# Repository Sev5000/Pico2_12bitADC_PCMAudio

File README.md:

# Pico2_12bitADC_PCMAudio
This is a PCB to neatly package a Raspberry Pi Pico 2, AD9226 ADC PCB and a PCM1802 audio board for capture with hsdaoh.
Specifically designed to still be usefull without smds (no head switch input then). Through-hole only works just fine.
For use with https://github.com/steve-m/hsdaoh-rp2350/tree/pcm1802

Features:
- The Pico 2 can be socketed with and without a DVI sock
- Mounting holes for the AD9226 pcb, PCM1802 and a socketed Pi Pico 2 with DVI sock (original and adafruit verfied)
- Audio input with either chinch or 3.5mm jack
- Jumper to choose between head switch input and clipping bit of the AD9226
- Protected head switch input has footprints for jst, as well as edge and horizontal SMA/SMB

Bill of material: 
- 1x This PCB (Send the Gerber .zip to JLC, PCBWay, ..)
- 1x Raspberry Pi Pico 2
- 1x AD9226: https://aliexpress.com/item/1005003038271519.html
- 1x PCM1802: https://aliexpress.com/item/1005006412873984.html
- 2x RCA-105 or RCA-106: https://aliexpress.com/item/1005006152724809.html
- 1x PJ-324M 5P: https://aliexpress.com/item/1005006146950431.html
- 1x 3pin 2.54mm pin header horizontal for the headswitch/overflow selection jumper
- 1x 9pin 2.54mm pin-socket header 
- 1x 2x10pin 2.54mm pin-socket header
- 1x 3pin 2.54mm pin header (remove the center pin for connecting R/L of the PCM1802)
- 1x 3pin 2.54mm pin-socket header (remove the center pin for connecting R/L of the PCM1802)

No SMD variant:
- 1x DVI-Sock: https://github.com/Wren6991/Pico-DVI-Sock for a flush fit with the pcb edge, otherwise the adafruit DVI sock works fine too
- 2x 15pin 2.54mm pin-socket header

SMD Variant:
- 1× Stewart SS-53000-001 connector (See https://github.com/Wren6991/Pico-DVI-Sock BOM for details)
- 8× 0402 270 ohm resistors
- 5x 0805 100nF ceramic capacitors
- 2x 20pin 2.54mm pin-socket header (For socketed Pi Pico 2 only)

For head switch input:
- 1x SOD123 3.3V zener diode
- 1x SOD123 standard diode
- 1x 0805 1k resistor
- 1x edge SMA/SMB or horizontal SMA/SMB and/or 2pin header

Notes:
The PCM1802 board needs MODE0 (MODE1 only with previous HSDAOH releases) bridged *and* connected to 3.3V with a wire (Those boards have a design error):
NOTE: Picture shows the configuration for the older firmware, now only MODE0 needs to be bridged and connected to 3.3V

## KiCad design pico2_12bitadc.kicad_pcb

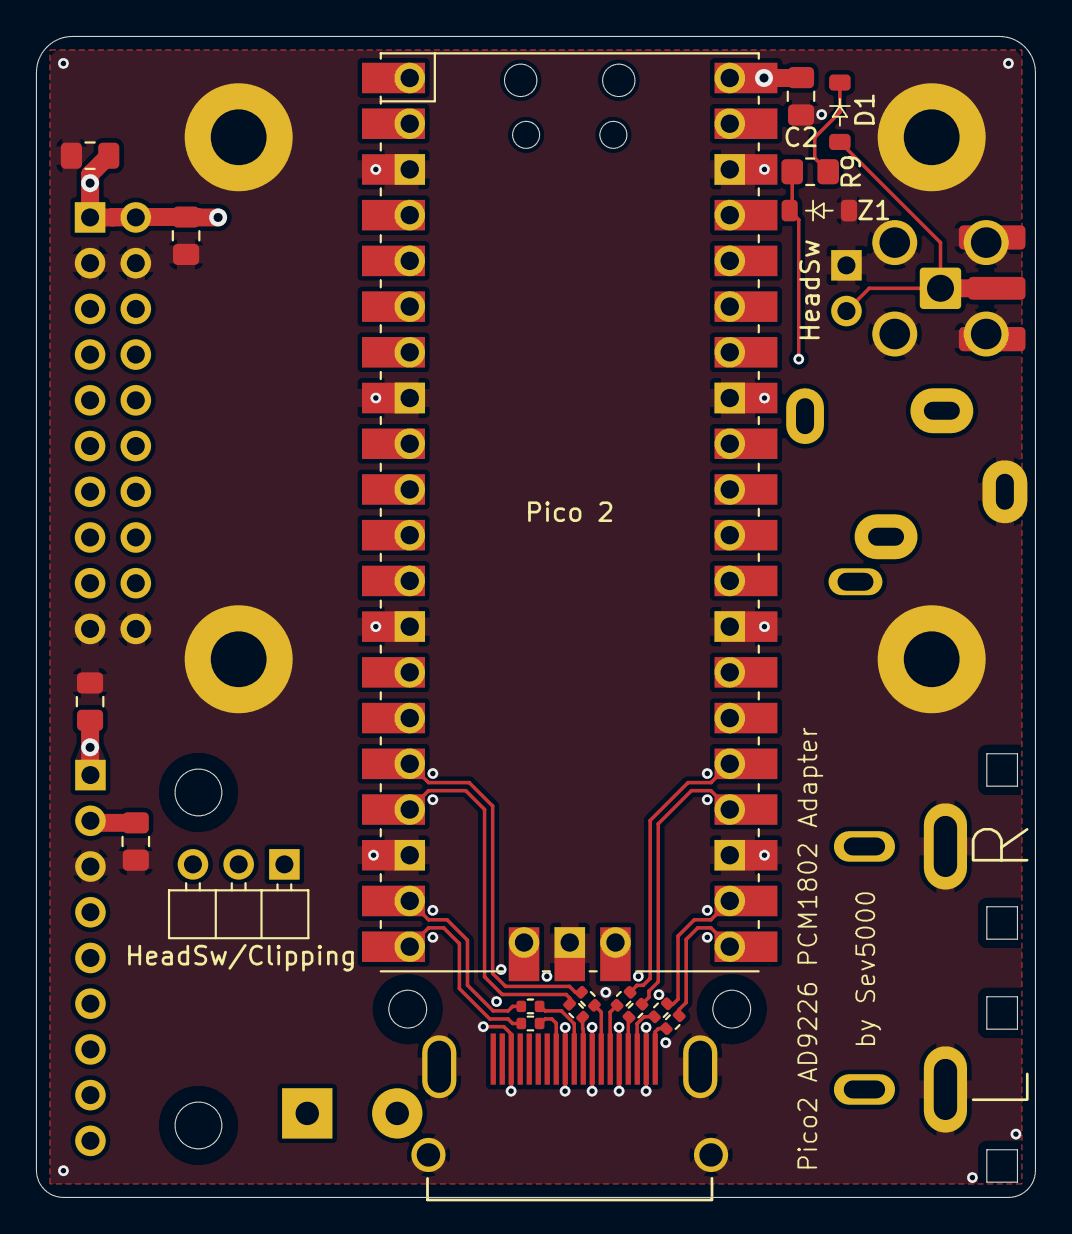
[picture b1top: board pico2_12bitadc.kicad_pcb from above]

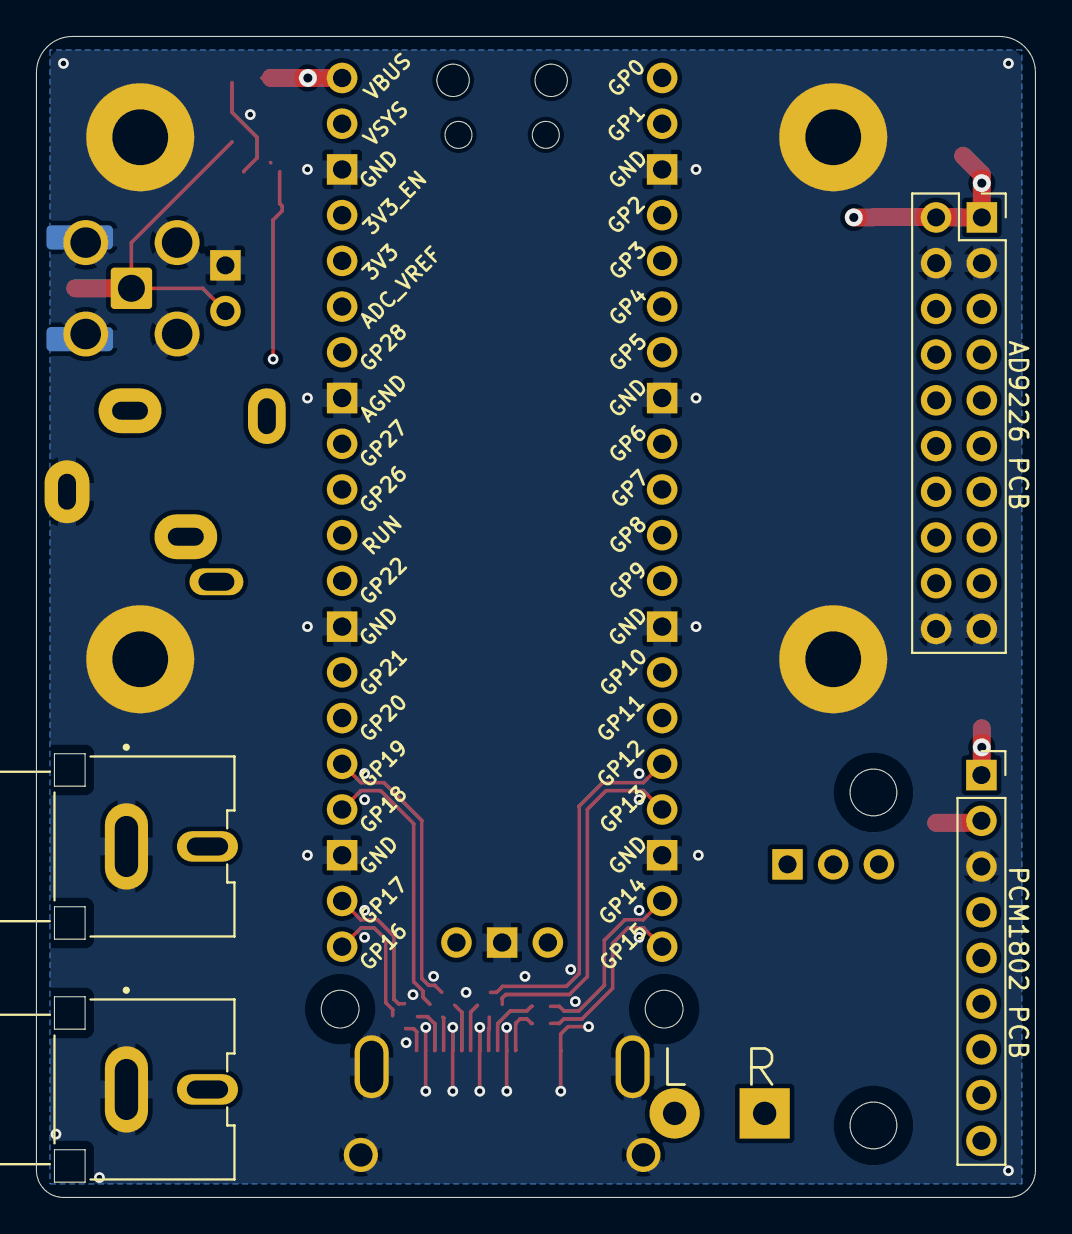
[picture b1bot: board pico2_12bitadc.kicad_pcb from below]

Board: 4 copper layers, 55.5 x 64.5 mm, 28 parts (4 on the bottom side), 43 nets.

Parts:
C1, C2, C3, C4, C5: 100nF; C_0805_2012Metric_Pad1.18x1.45mm_HandSolder
D1: D; D_SOD-123
J1: NOT_HDMI_A; HDMI-SS-53000
J2: PCM1802 PCB; PinSocket_1x09_P2.54mm_Vertical
J3: AD9226 PCB; PinSocket_2x10_P2.54mm_Vertical
J4: L R; TerminalBlock_MaiXu_MX126-5.0-02P_1x02_P5.00mm
J5: L; CUI_RCJ-047
J6: HeadSw/Clipping; PinHeader_1x03_P2.54mm_Horizontal
J7: R; CUI_RCJ-047
J8: AudioJack2_Ground_Switch; Jack_3.5mm_CUI_SJ1-3515N_Horizontal
J9: HeadSw; PinHeader_1x02_P2.54mm_Horizontal
J10: SMA90; SMA_Amphenol_901-143_Horizontal
J11: SMAEdge; SMA_Samtec_SMA-J-P-H-ST-EM1_EdgeMount
Pico 2: Pico; RPi_Pico_SMD_TH
R1, R2, R3, R4, R5, R6, R7, R8: 270; R_0402_1005Metric
R9: 1k; R_0805_2012Metric_Pad1.20x1.40mm_HandSolder
Z1: D_Zener3.3V; D_SOD-123

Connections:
+5V: C1.1, C2.1, C4.1, C5.1, J1.18 (+5V), J2.5V (Pin_1), J3.5V (Pin_1), Pico 2.40 (VBUS)
/CK+: J1.10 (CK+), R7.2
/CK-: J1.12 (CK-), R8.2
/D0+: J1.7 (D0+), R5.2
/D0-: J1.9 (D0-), R6.2
/D1+: J1.4 (D1+), R3.2
/D1-: J1.6 (D1-), R4.2
/D2+: J1.1 (D2+), R1.2
/D2-: J1.3 (D2-), R2.2
/PICO_CK+: Pico 2.19 (GPIO14), R7.1
/PICO_CK-: Pico 2.20 (GPIO15), R8.1
/PICO_D0+: Pico 2.16 (GPIO12), R5.1
/PICO_D0-: Pico 2.17 (GPIO13), R6.1
/PICO_D1+: Pico 2.24 (GPIO18), R3.1
/PICO_D1-: Pico 2.25 (GPIO19), R4.1
/PICO_D2+: Pico 2.21 (GPIO16), R1.1
/PICO_D2-: Pico 2.22 (GPIO17), R2.1
GND: C1.2, C2.2, C3.2, C4.2, C5.2, J1.2 (D2S), J1.5 (D1S), J1.8 (D0S), J1.11 (CKS), J1.17 (GND), J1.SH, J2.GND (Pin_3), J3.GND (Pin_4), J5.1 (In), J7.1 (In), J8.S, J9.1, J10.2 (Ext), J11.2 (Ext), Pico 2.3 (GND), Pico 2.8 (GND), Pico 2.13 (GND), Pico 2.18 (GND), Pico 2.23 (GND), Pico 2.28 (GND), Pico 2.33 (AGND), Pico 2.38 (GND), Pico 2.42 (GND), Z1.2 (A)
unnamed: D1.2 (A), J9.2, J10.1 (In), J11.1 (In)
unnamed: D1.1 (K), R9.1
unnamed: J6.1, R9.2, Z1.1 (K)
unnamed: C3.1, J2.3.3V (Pin_2), J2.PDW (Pin_8)
unnamed: J2.DOUT (Pin_4), Pico 2.29 (GPIO22)
unnamed: J2.BCK (Pin_5), Pico 2.31 (GPIO26_ADC0)
unnamed: J2.LRCK (Pin_7), Pico 2.32 (GPIO27_ADC1)
unnamed: J2.SCK (Pin_9), Pico 2.27 (GPIO21)
unnamed: J3.CLK (Pin_5), Pico 2.26 (GPIO20)
unnamed: J3.D0 (Pin_6), Pico 2.1 (GPIO0)
unnamed: J3.D1 (Pin_7), Pico 2.2 (GPIO1)
unnamed: J3.D2 (Pin_8), Pico 2.4 (GPIO2)
unnamed: J3.D3 (Pin_9), Pico 2.5 (GPIO3)
unnamed: J3.D4 (Pin_10), Pico 2.6 (GPIO4)
unnamed: J3.D5 (Pin_11), Pico 2.7 (GPIO5)
unnamed: J3.D6 (Pin_12), Pico 2.9 (GPIO6)
unnamed: J3.D7 (Pin_13), Pico 2.10 (GPIO7)
unnamed: J3.D8 (Pin_14), Pico 2.11 (GPIO8)
unnamed: J3.D9 (Pin_15), Pico 2.12 (GPIO9)
unnamed: J3.D10 (Pin_16), Pico 2.14 (GPIO10)
unnamed: J3.D11 (Pin_17), Pico 2.15 (GPIO11)
unnamed: J3.OTR (Pin_18), J6.3
unnamed: J4.1, J7.2 (Ext), J8.R
unnamed: J4.2, J5.2 (Ext), J8.T
unnamed: J6.2, Pico 2.34 (GPIO28_ADC2)

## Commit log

2024-12-08 Update README.md
    Embed render
2025-01-04 Update pico2_12bitadc.kicad_pcb
    Fixed hole spacing of the ad9226 pcb footprint
2025-01-04 Update pico2_12bitadc.kicad_pcb
    Fixed trace near new hole position
2025-01-04 Update pico2_12bitadc.kicad_pcb
    Added Name
2025-01-04 Update pico2_12bitadc.kicad_pcb
    Minor silkscreen adjustments
2025-01-06 Update pico2_12bitadc.kicad_pcb
    Increased pad length and through hole size of the hdmi connector for better compatability with other connector models
2025-02-03 Add Gerber Files
2025-03-30 Update README.md
    Change PCM config to match the latest HSDAOH release
